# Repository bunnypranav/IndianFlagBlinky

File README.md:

# Indian flag Blinky

This is my version of the Blueprint "Blinky Board", but redesigned around the Indian flag. It uses 9 LEDs, 4 in the top row, 4 in the bottom, and 1 in the middle to represent the "Ashoka Chakra", or the blue coloured wheel in the center of the flag. The blinking of the LEDs also creates a wave effect that mimics the movement of the flag in the wind. All the other circuitry is below the 2:3 rectangle of the flag, the same as described in the Flag Code of India. I have also added a small logo with my name and my characteristic "Bunny". The inspiration for this project came from the maple leaf board in the guide, and I wanted to create something similar for my home country of India.

The circuit is based on a 555 timer in astable mode driving a CD4017 decade counter, which sequentially lights up 10 LEDs.

# PCB
*Made in KiCad*

# BOM:
* PCB (with Shipping) - USD 10.5
* LED IC 4017
* 1 uF Capacitor
* 0.01 uF Capacitor
* LEDs,9,Kit
* PinHeader 1x01
* PinHeader 1x02
* Timer IC NE555P
* 1KΩ Re
* 470Ω Re
* Potentiometer 50K
* USB-C-TH_TYPE-C-31-M-33 header (self sourced)

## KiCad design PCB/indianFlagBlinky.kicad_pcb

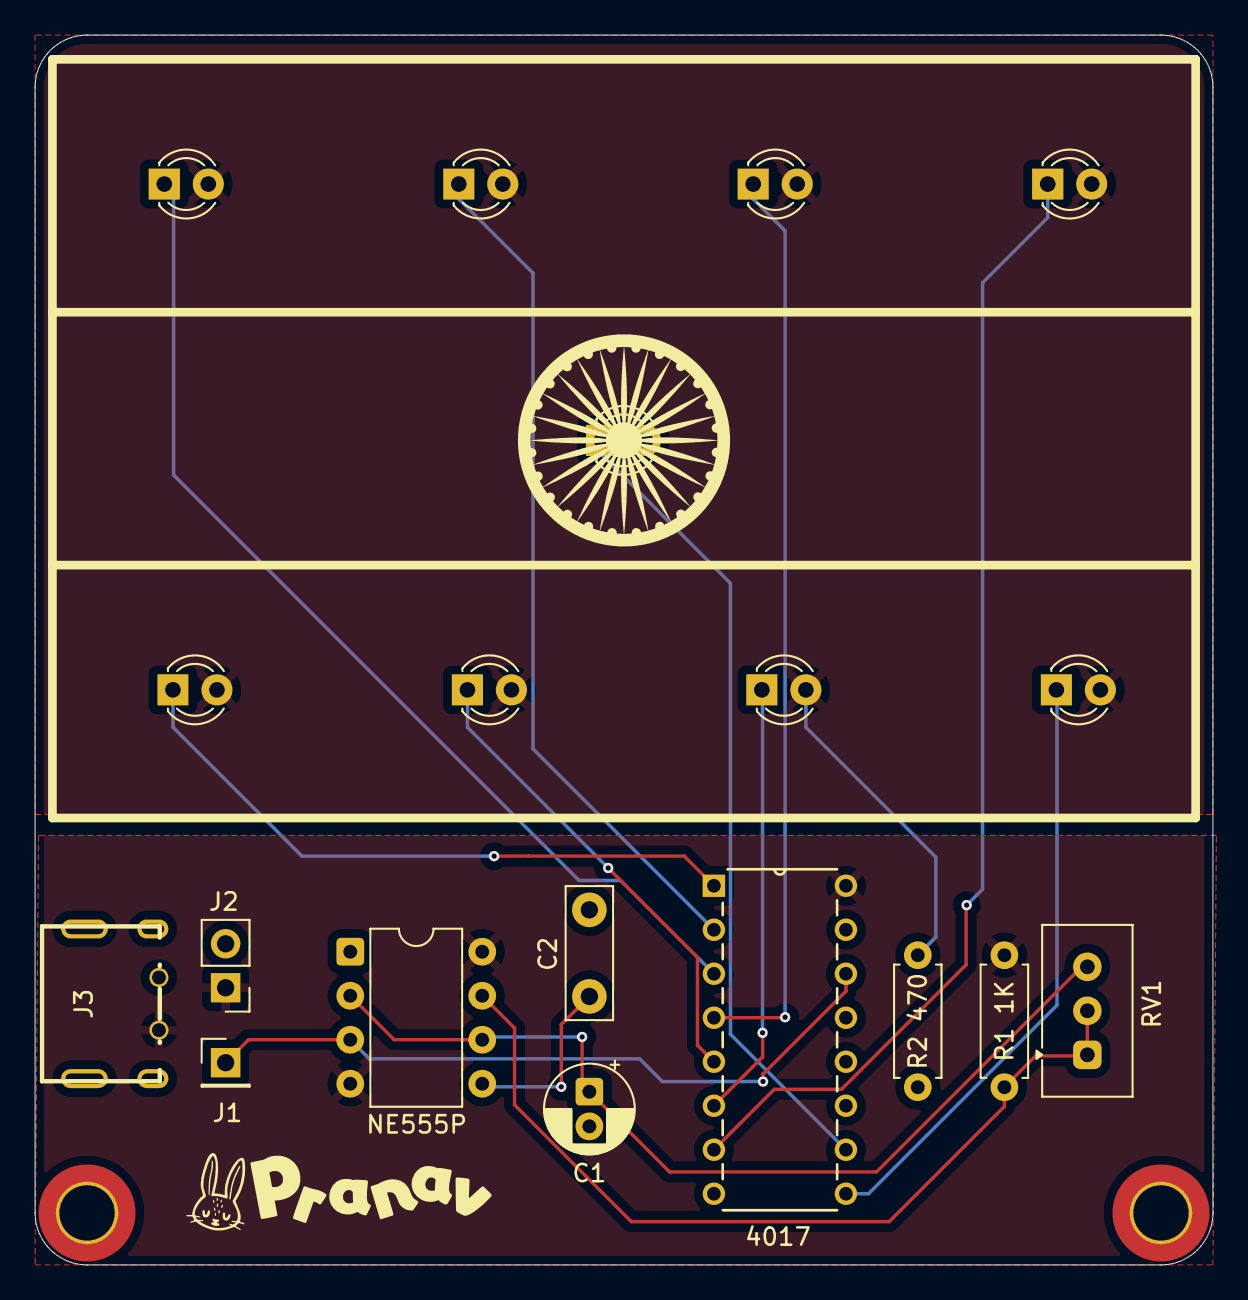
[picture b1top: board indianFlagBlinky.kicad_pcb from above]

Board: 2 copper layers, 68.0 x 71.0 mm, 22 parts (1 on the bottom side), 16 nets.

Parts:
4017: 4017; N16
C1: 1 uF; CP_Radial_D5.0mm_P2.00mm
C2: 0.01 uF; C_Disc_D7.5mm_W2.5mm_P5.00mm
D1, D2, D3, D4, D5, D6, D7, D8, D9: LED; LED_D3.0mm
J1: Conn_01x01_Socket; PinHeader_1x01_P2.54mm_Vertical
J2: Conn_01x02_Socket; PinHeader_1x02_P2.54mm_Vertical
J3: USB_C_Receptacle_PowerOnly_6P; USB-C-TH_TYPE-C-31-M-33
NE555P: NE555P; DIP-8_W7.62mm
R1 1K: 1KΩ; R_Axial_DIN0207_L6.3mm_D2.5mm_P7.62mm_Horizontal
R2 470: 470Ω; R_Axial_DIN0207_L6.3mm_D2.5mm_P7.62mm_Horizontal
RV1: 50kΩ; Potentiometer_Vishay_T93YA_Vertical
S1, S2: MountingHole_3.2mm_M3_DIN965_Pad_TopBottom
back: LOGO

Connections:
+5V: 4017.16 (VDD), J2.1, J3.A9 (VBUS), NE555P.4 (~RST), NE555P.8 (VCC), R1 1K.1
GND: 4017.8 (VSS), 4017.13 (CKEN), 4017.15 (Reset), C1.2, C2.2, J2.2, J3.B12 (GND), NE555P.1 (GND), R2 470.2, S1.1, S2.1
LED2R: D1.2 (A), D2.2 (A), D3.2 (A), D4.2 (A), D5.2 (A), D6.2 (A), D7.2 (A), D8.2 (A), D9.2 (A), R2 470.1
unnamed: 4017.3 (Q0), D1.1 (K)
unnamed: 4017.2 (Q1), D2.1 (K)
unnamed: 4017.4 (Q2), D3.1 (K)
unnamed: 4017.7 (Q3), D4.1 (K)
unnamed: 4017.10 (Q4), D5.1 (K)
unnamed: 4017.1 (Q5), D6.1 (K)
unnamed: 4017.5 (Q6), D7.1 (K)
unnamed: 4017.6 (Q7), D8.1 (K)
unnamed: 4017.9 (Q8), D9.1 (K)
unnamed: C2.1, NE555P.5 (CONT)
unnamed: NE555P.7 (DISCH), R1 1K.2, RV1.1, RV1.2
OUT: 4017.14 (CLK), J1.1, NE555P.3 (OUT)
TRIG: C1.1, NE555P.2 (TRIG), NE555P.6 (THRES), RV1.3
